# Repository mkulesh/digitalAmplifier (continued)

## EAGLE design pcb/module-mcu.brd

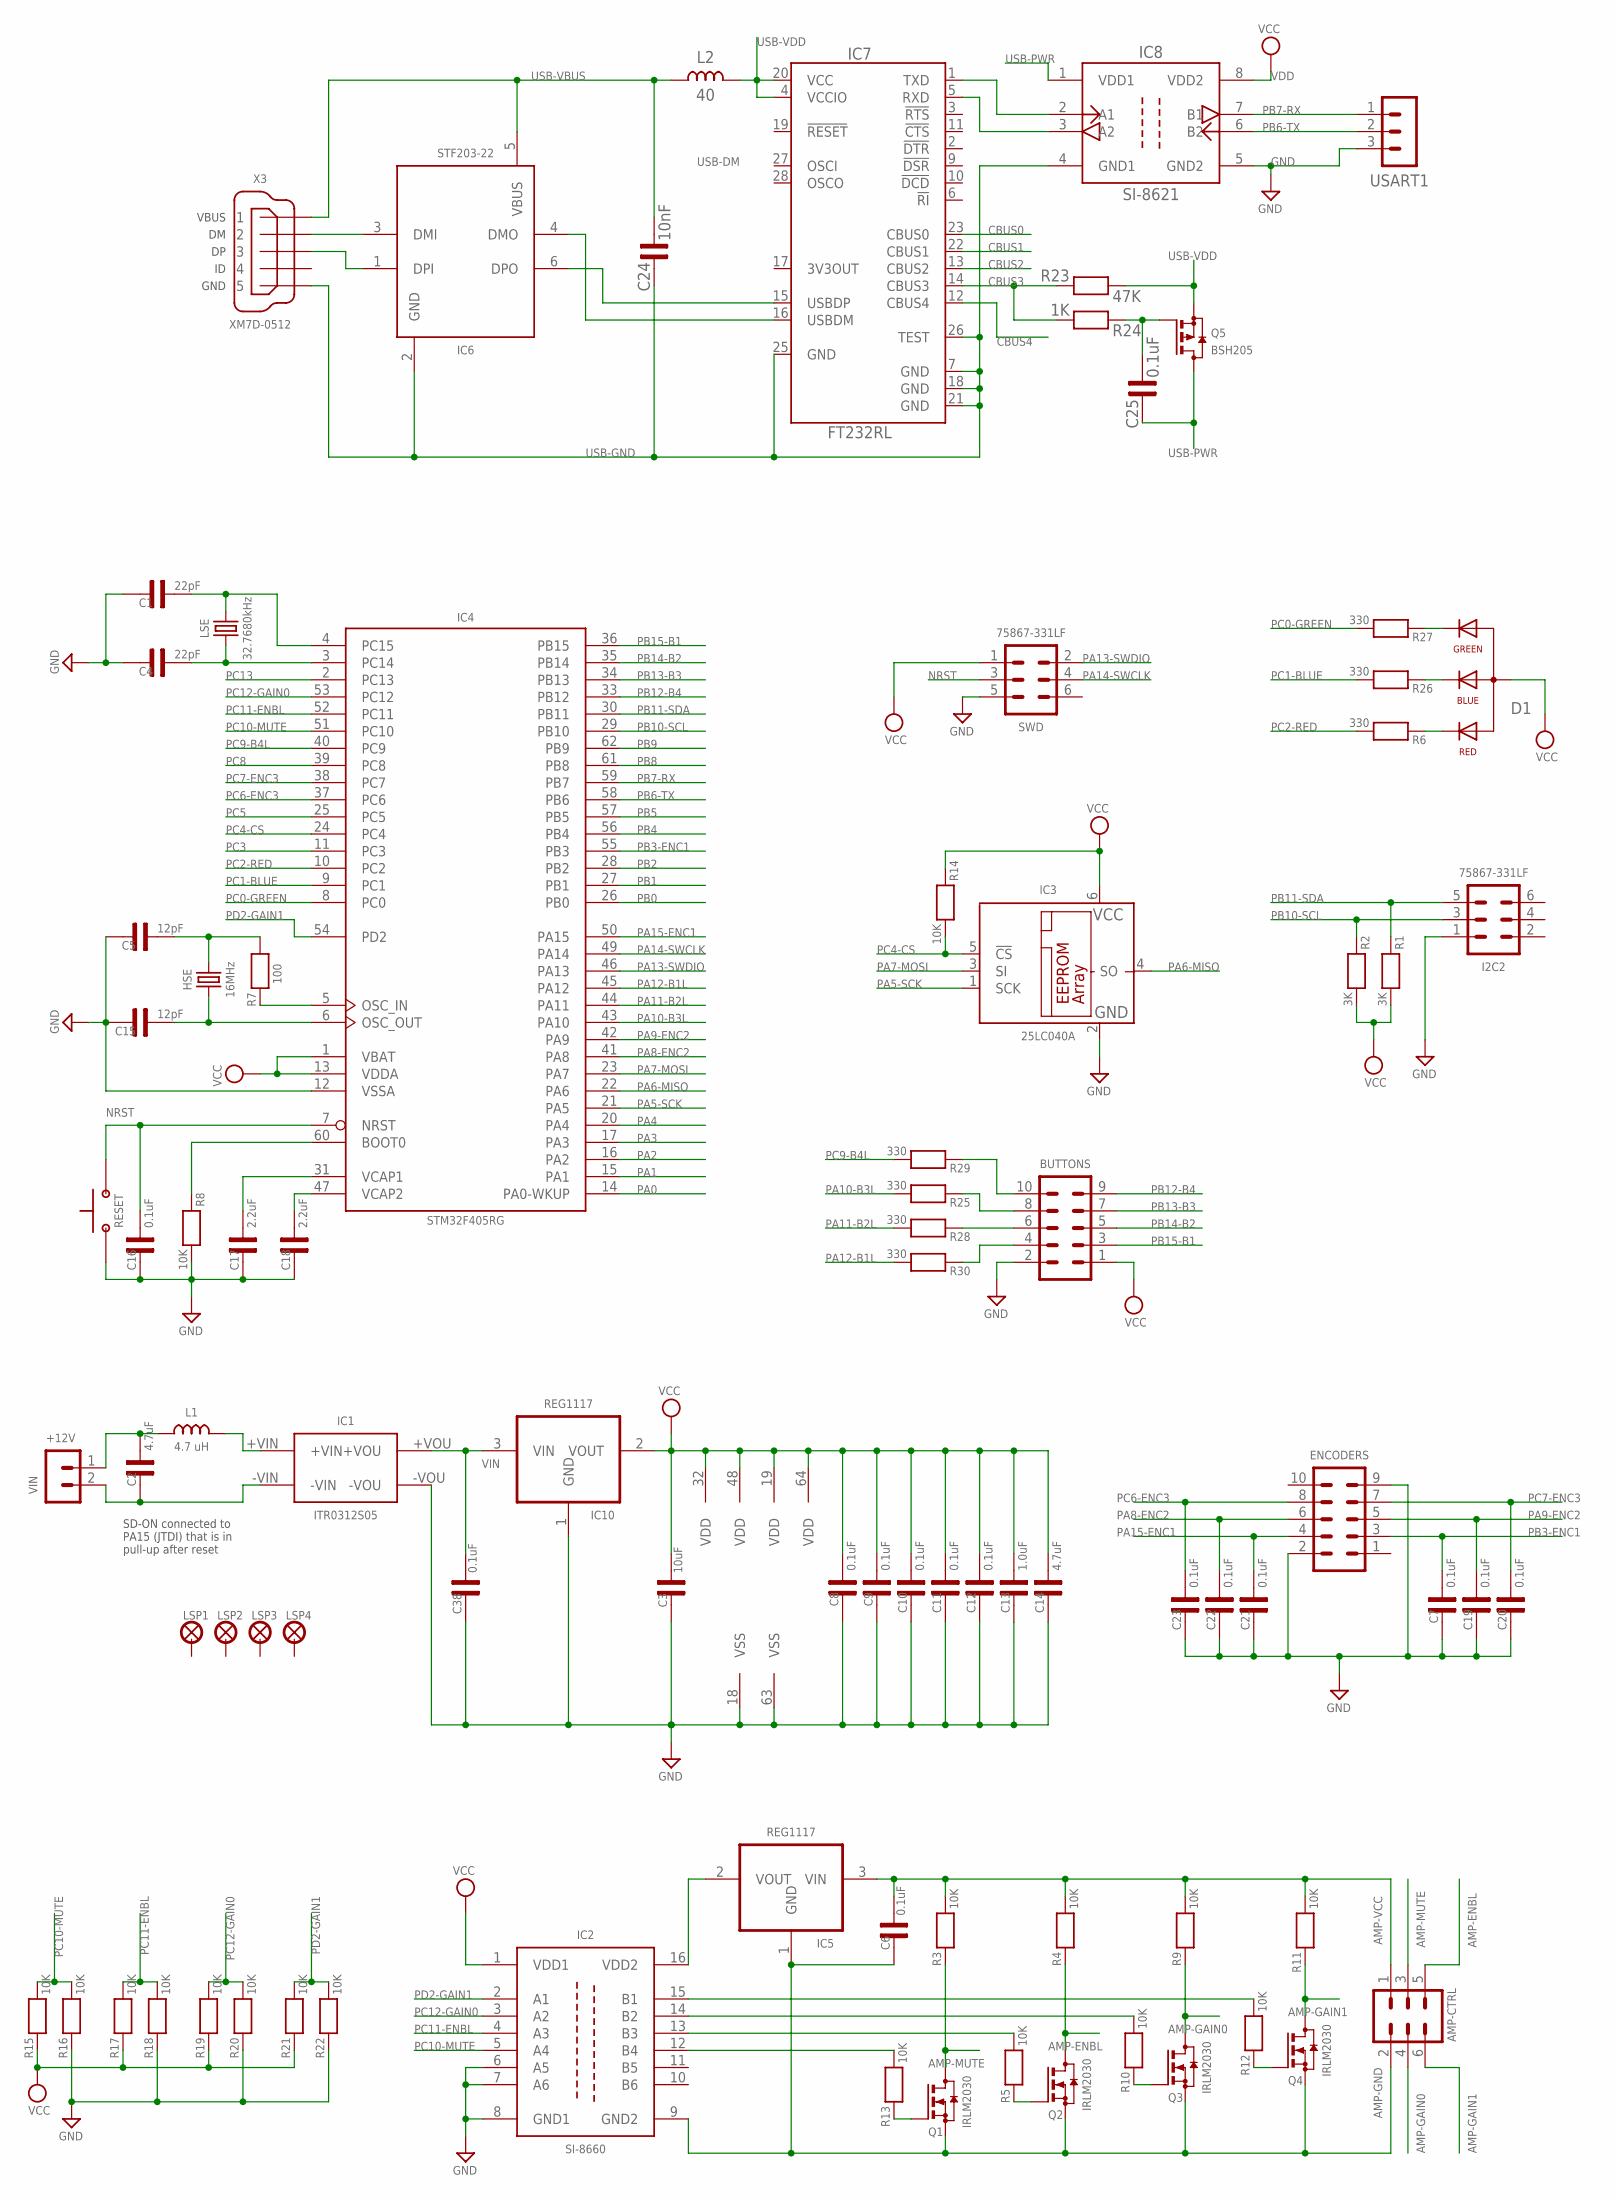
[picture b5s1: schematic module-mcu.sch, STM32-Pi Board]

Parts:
AMP-CTRL: MA03-2PL; MA03-2
BUTTONS: MA05-2
C1, C4: 22pF; C0805
C2: 4.7uF; C1206
C3: 10uF; C0805
C5, C15: 12pF; C0805
C6, C7, C8, C9, C10, C11, C12, C16, C19, C20, C21, C22, C23, C25, C38: 0.1uF; C0805
C13: 1.0uF; C0805
C14: 4.7uF; C0805
C17, C18: 2.2uF; C0805
C24: 10nF; C0805
D1: RGB-LED3X1MM; RGB-LED-SMD-3X1
ENCODERS: MA05-2
HSE: 16MHz; Q-HC-46X
I2C2: 75867-331LF; MA03-2
IC1: ITR0312S05
IC2: SI-8660; SO16
IC3: 25LC040A; SOT23-6
IC4: STM32F405RG; LQFP64
IC5, IC10: REG1117; SOT223
IC6: STF203-22; SC70-6
IC7: FT232RL; SSOP28
IC8: SI-8621; SOIC-8
L1: 4.7 uH; L0805
L2: 40; L0805
LSE: 32.7680kHz; Q-CM7V-T1A
LSP1, LSP2, LSP3, LSP4: LSP27
Q1, Q2, Q3, Q4: IRLM2030; SOT23
Q5: BSH205; SOT23
R1, R2: 3K; R0805
R3, R4, R5, R8, R9, R10, R11, R12, R13, R14, R15, R16, R17, R18, R19, R20, R21, R22: 10K; R0805
R6, R25, R26, R27, R28, R29, R30: 330; R0805
R7: 100; R0805
R23: 47K; R0805
R24: 1K; R0805
RESET: BUTTON-FSM14JRT
SWD: 75867-331LF; MA03-2-BLUE
USART1: MA03-1PL; MA03-1
VIN: MA02-1GREEN; MA02-1-GREEN
X3: XM7D-0512

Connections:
AMP-ENBL: AMP-CTRL.5, Q2.3 (D), R4.1
AMP-GAIN0: AMP-CTRL.4, Q3.3 (D), R9.1
AMP-GAIN1: AMP-CTRL.6, Q4.3 (D), R11.1
AMP-GND: AMP-CTRL.2, C6.1, IC2.9 (GND2), IC5.1 (GND), Q1.2 (S), Q2.2 (S), Q3.2 (S), Q4.2 (S)
AMP-MUTE: AMP-CTRL.3, Q1.3 (D), R3.1
AMP-VCC: AMP-CTRL.1, C6.2, IC5.3 (VIN), R3.2, R4.2, R9.2, R11.2
BOOT: IC4.60 (BOOT0), R8.1
CBUS0: IC7.23 (CBUS0)
CBUS1: IC7.22 (CBUS1)
CBUS2: IC7.13 (CBUS2)
CBUS3: IC7.14 (CBUS3), R23.1, R24.2
CBUS4: IC7.12 (CBUS4)
GND: BUTTONS.2, C1.1, C3.1, C4.1, C5.1, C7.1, C8.1, C9.1, C10.1, C11.1, C12.1, C13.1, C14.1, C15.1, C16.1, C17.1, C18.1, C19.1, C20.1, C21.1, C22.1, C23.1, C38.1, ENCODERS.2, ENCODERS.9, I2C2.1, IC1.-VOU, IC2.6 (A5), IC2.7 (A6), IC2.8 (GND1), IC3.2 (GND), IC4.12 (VSSA), IC4.18 (VSS), IC4.63 (VSS), IC8.5 (GND2), IC10.1 (GND), R8.2, R16.1, R18.1, R20.1, R22.1, RESET.P$1 (1), SWD.5, USART1.3
unnamed: C2.1, IC1.-VIN, VIN.2
unnamed: D1.P$1 (AR), R6.1
unnamed: IC4.5 (OSC_IN), R7.1
unnamed: IC1.+VIN, L1.2
unnamed: C2.2, L1.1, VIN.1
unnamed: Q2.1 (G), R5.1
unnamed: Q1.1 (G), R13.1
unnamed: IC2.12 (B4), R13.2
unnamed: IC2.13 (B3), R5.2
unnamed: Q3.1 (G), R10.1
unnamed: IC2.14 (B2), R10.2
unnamed: Q4.1 (G), R12.1
unnamed: IC2.15 (B1), R12.2
unnamed: IC2.16 (VDD2), IC5.2 (VOUT)
unnamed: IC6.1 (DPI), X3.3
unnamed: D1.P$4 (AB), R26.1
unnamed: IC6.3 (DMI), X3.2
unnamed: IC7.1 (TXD), IC8.2 (A1)
unnamed: IC7.5 (RXD), IC8.3 (A2)
unnamed: C25.2, Q5.1 (G), R24.1
unnamed: BUTTONS.4, R30.1
unnamed: BUTTONS.6, R28.1
unnamed: BUTTONS.8, R25.1
unnamed: BUTTONS.10, R29.1
unnamed: C5.2, HSE.1, R7.2
unnamed: D1.P$3 (AG), R27.1
unnamed: C15.2, HSE.2, IC4.6 (OSC_OUT)
NRST: C16.2, IC4.7 (NRST), RESET.P$2 (2), SWD.3
PA0: IC4.14 (PA0-WKUP)
PA1: IC4.15 (PA1)
PA2: IC4.16 (PA2)
PA3: IC4.17 (PA3)
PA4: IC4.20 (PA4)
PA5-SCK: IC3.1 (SCK), IC4.21 (PA5)
PA6-MISO: IC3.4 (SO), IC4.22 (PA6)
PA7-MOSI: IC3.3 (SI), IC4.23 (PA7)
PA8-ENC2: C22.2, ENCODERS.6, IC4.41 (PA8)
PA9-ENC2: C19.2, ENCODERS.5, IC4.42 (PA9)
PA10-B3L: IC4.43 (PA10), R25.2
PA11-B2L: IC4.44 (PA11), R28.2
PA12-B1L: IC4.45 (PA12), R30.2
PA13-SWDIO: IC4.46 (PA13), SWD.2
PA14-SWCLK: IC4.49 (PA14), SWD.4
PA15-ENC1: C21.2, ENCODERS.4, IC4.50 (PA15)
PB0: IC4.26 (PB0)
PB1: IC4.27 (PB1)
PB2: IC4.28 (PB2)
PB3-ENC1: C7.2, ENCODERS.3, IC4.55 (PB3)
PB4: IC4.56 (PB4)
PB5: IC4.57 (PB5)
PB6-TX: IC4.58 (PB6), IC8.6 (B2), USART1.2
PB7-RX: IC4.59 (PB7), IC8.7 (B1), USART1.1
PB8: IC4.61 (PB8)
PB9: IC4.62 (PB9)
PB10-SCL: I2C2.3, IC4.29 (PB10), R2.1
PB11-SDA: I2C2.5, IC4.30 (PB11), R1.1
PB12-B4: BUTTONS.9, IC4.33 (PB12)
PB13-B3: BUTTONS.7, IC4.34 (PB13)
PB14-B2: BUTTONS.5, IC4.35 (PB14)
PB15-B1: BUTTONS.3, IC4.36 (PB15)
PC0-GREEN: IC4.8 (PC0), R27.2
PC1-BLUE: IC4.9 (PC1), R26.2
PC2-RED: IC4.10 (PC2), R6.2
PC3: IC4.11 (PC3)
PC4-CS: IC3.5 (!CS), IC4.24 (PC4), R14.2
PC5: IC4.25 (PC5)
PC6-ENC3: C23.2, ENCODERS.8, IC4.37 (PC6)
PC7-ENC3: C20.2, ENCODERS.7, IC4.38 (PC7)
PC8: IC4.39 (PC8)
PC9-B4L: IC4.40 (PC9), R29.2
PC10-MUTE: IC2.5 (A4), IC4.51 (PC10), R15.2, R16.2
PC11-ENBL: IC2.4 (A3), IC4.52 (PC11), R17.2, R18.2
PC12-GAIN0: IC2.3 (A2), IC4.53 (PC12), R19.2, R20.2
PC13: IC4.2 (PC13)
PD2-GAIN1: IC2.2 (A1), IC4.54 (PD2), R21.2, R22.2
Q2M: C4.2, IC4.3 (PC14), LSE.1
Q2P: C1.2, IC4.4 (PC15), LSE.2
USB-DM: IC6.4 (DMO), IC7.16 (USBDM)
USB-DP: IC6.6 (DPO), IC7.15 (USBDP)
USB-GND: C24.1, IC6.2 (GND), IC7.7 (GND), IC7.18 (GND), IC7.21 (GND), IC7.25 (GND), IC7.26 (TEST), IC8.4 (GND1), X3.5
USB-PWR: C25.1, IC8.1 (VDD1), Q5.3 (D)
USB-VBUS: C24.2, IC6.5 (VBUS), L2.1, X3.1
USB-VDD: IC7.4 (VCCIO), IC7.20 (VCC), L2.2, Q5.2 (S), R23.2
VCAP3: C18.2, IC4.47 (VCAP2)
VCAP4: C17.2, IC4.31 (VCAP1)
VDD: BUTTONS.1, C3.2, C8.2, C9.2, C10.2, C11.2, C12.2, C13.2, C14.2, D1.P$2 (C), IC2.1 (VDD1), IC3.6 (VCC), IC4.1 (VBAT), IC4.13 (VDDA), IC4.19 (VDD), IC4.32 (VDD), IC4.48 (VDD), IC4.64 (VDD), IC8.8 (VDD2), IC10.2 (VOUT), R1.2, R2.2, R14.1, R15.1, R17.1, R19.1, R21.1, SWD.1
VIN: C38.2, IC1.+VOU, IC10.3 (VIN)

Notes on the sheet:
SD-ON connected to PA15 (JTDI) that is in pull-up after reset

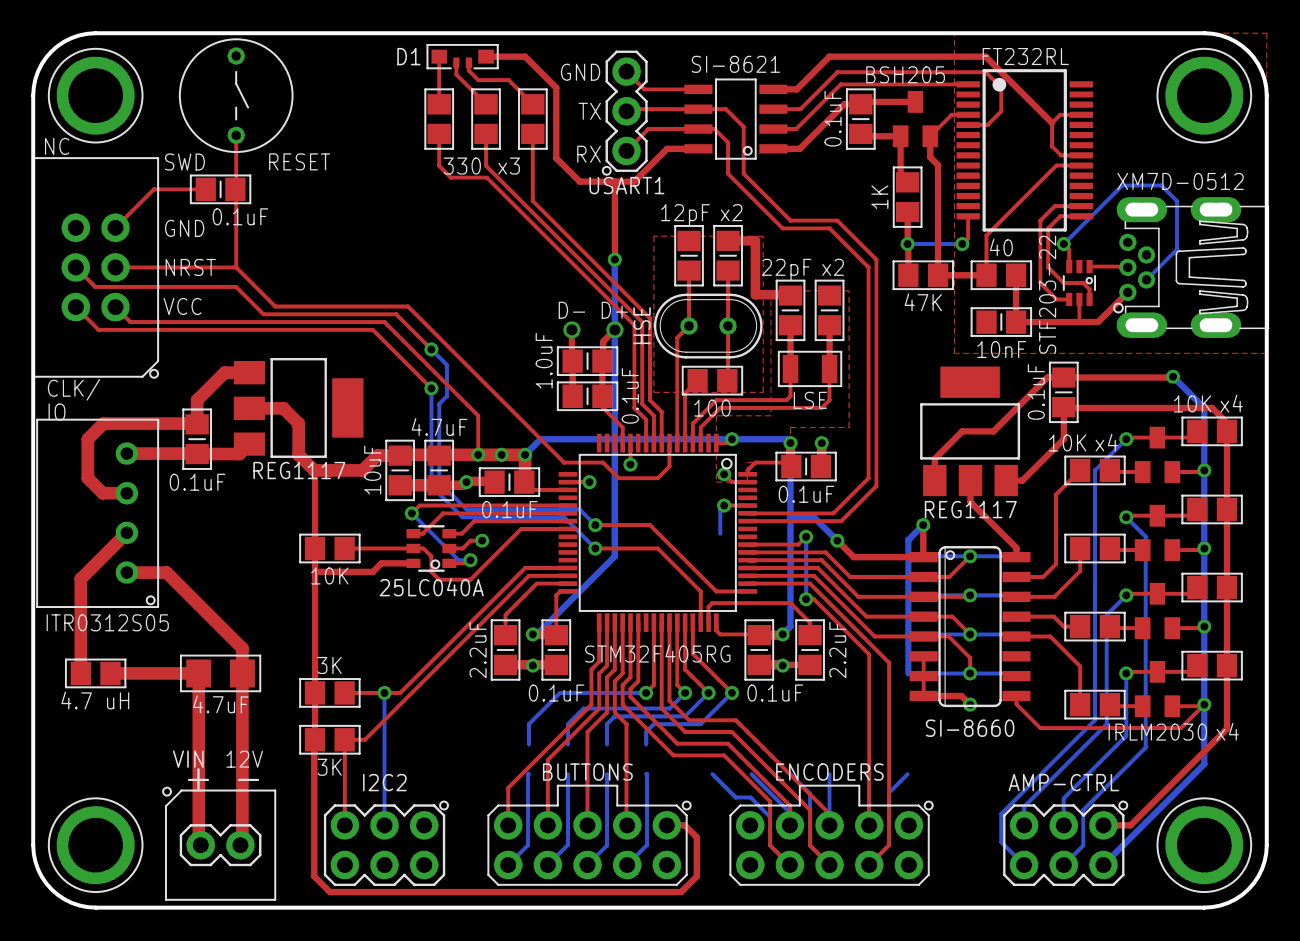
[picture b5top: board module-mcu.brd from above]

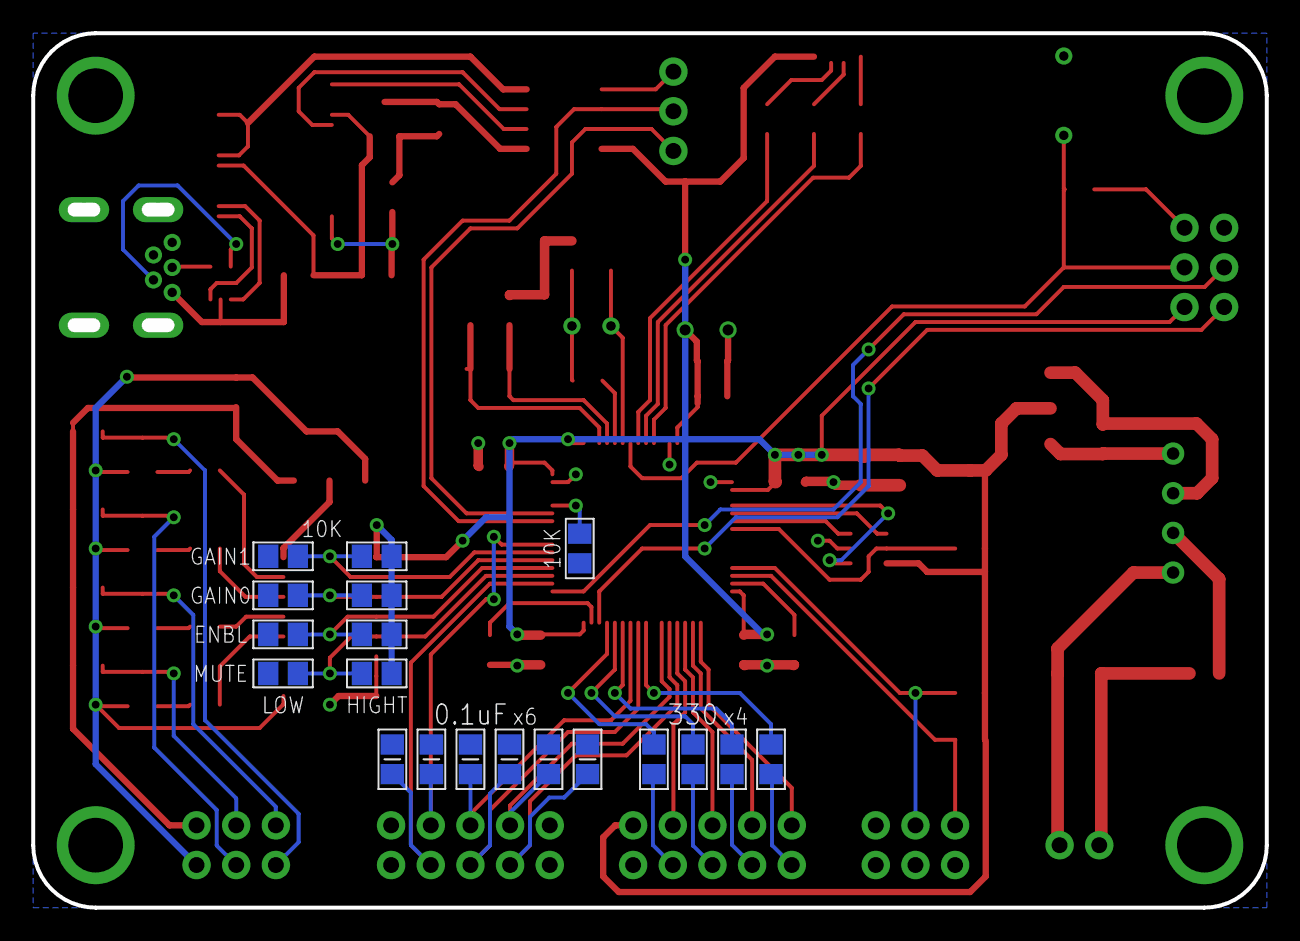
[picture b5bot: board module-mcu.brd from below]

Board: 2 copper layers, 78.4 x 55.4 mm, 88 parts (19 on the bottom side), 80 nets.

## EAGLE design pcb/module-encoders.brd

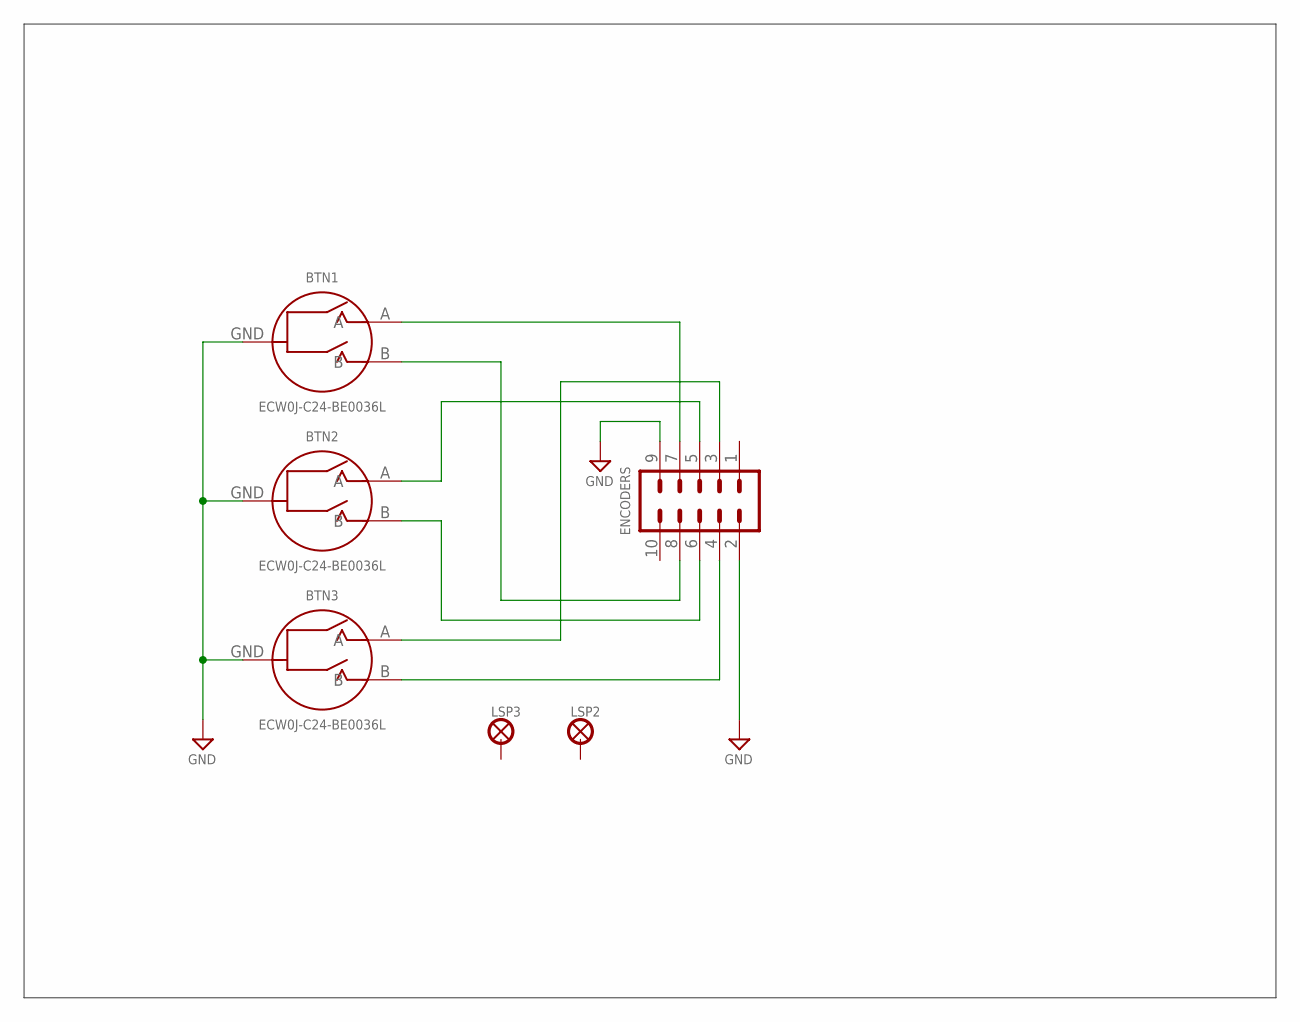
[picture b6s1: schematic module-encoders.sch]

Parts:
BTN1, BTN2, BTN3: ECW0J-C24-BE0036L; ECW0J-C24
ENCODERS: MA05-2
LSP2, LSP3: LSP27

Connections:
GND: BTN1.GND, BTN2.GND, BTN3.GND, ENCODERS.2, ENCODERS.9
unnamed: BTN3.B, ENCODERS.4
unnamed: BTN2.B, ENCODERS.6
unnamed: BTN1.B, ENCODERS.8
unnamed: BTN2.A, ENCODERS.5
unnamed: BTN1.A, ENCODERS.7
unnamed: BTN3.A, ENCODERS.3

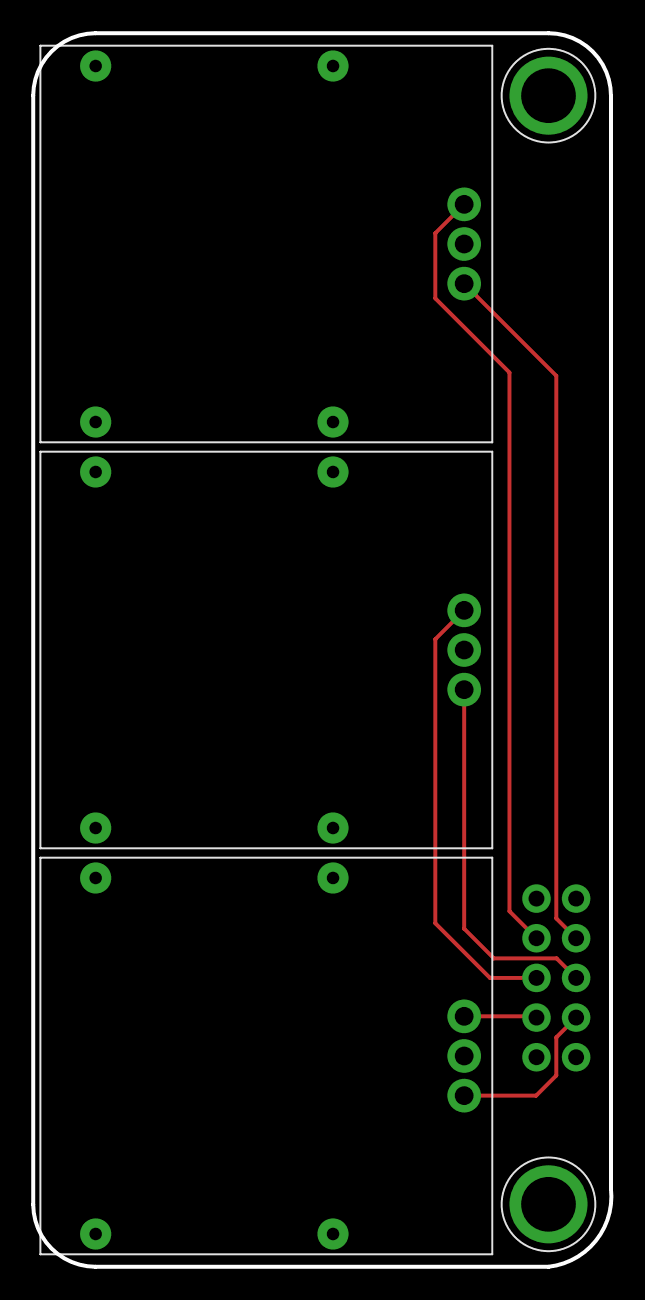
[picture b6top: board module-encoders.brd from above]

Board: 2 copper layers, 37.0 x 79.0 mm, 6 parts (1 on the bottom side), 7 nets.

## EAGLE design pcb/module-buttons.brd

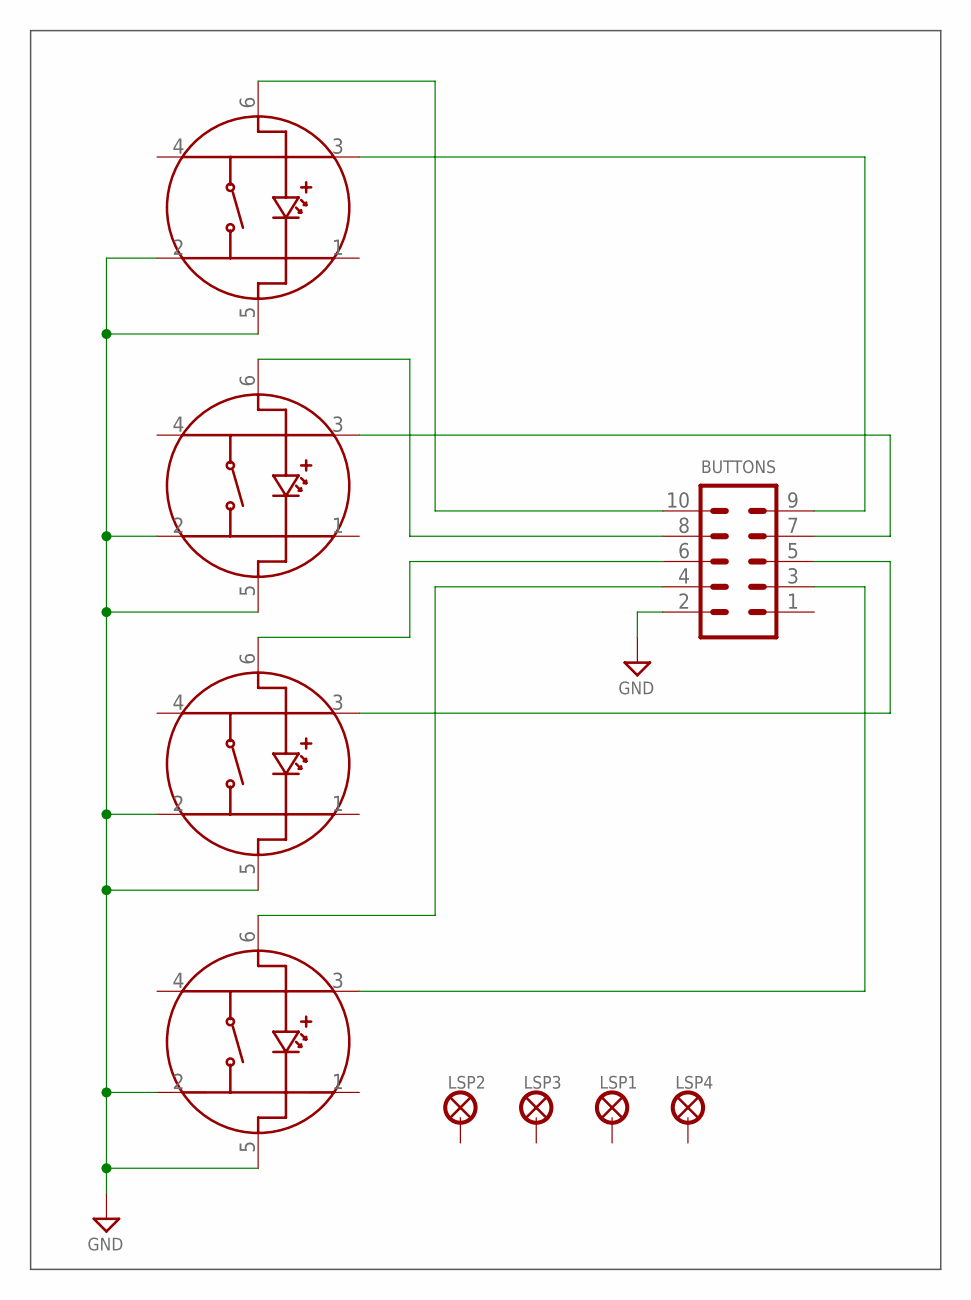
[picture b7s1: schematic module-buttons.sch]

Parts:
BTN1, BTN2, BTN3, BTN4: BUTTON-TL1265
BUTTONS: MA05-2
LSP1, LSP2, LSP3, LSP4: LSP27

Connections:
GND: BTN1.2, BTN1.5, BTN2.2, BTN2.5, BTN3.2, BTN3.5, BTN4.2, BTN4.5, BUTTONS.2
unnamed: BTN3.6, BUTTONS.6
unnamed: BTN2.3, BUTTONS.7
unnamed: BTN1.3, BUTTONS.9
unnamed: BTN3.3, BUTTONS.5
unnamed: BTN4.3, BUTTONS.3
unnamed: BTN4.6, BUTTONS.4
unnamed: BTN2.6, BUTTONS.8
unnamed: BTN1.6, BUTTONS.10

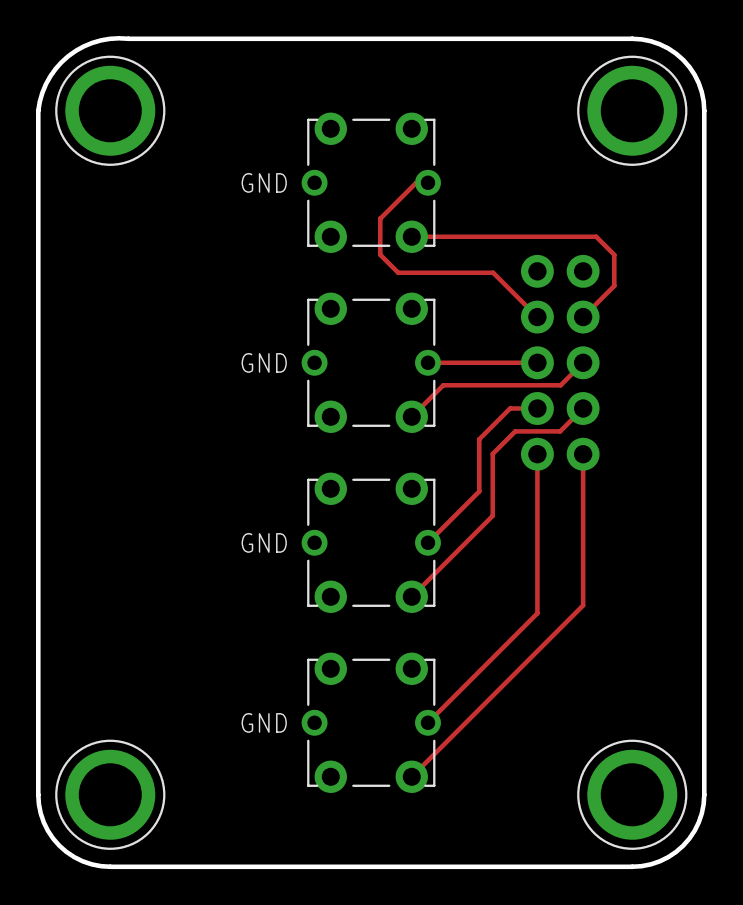
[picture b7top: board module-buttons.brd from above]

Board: 2 copper layers, 37.0 x 46.0 mm, 9 parts (1 on the bottom side), 9 nets.

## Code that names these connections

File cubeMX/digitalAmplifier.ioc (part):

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Mcu.Name=STM32F405RGTx
Mcu.Package=LQFP64
Mcu.UserName=STM32F405RGTx
PA10.GPIOParameters=GPIO_Label
PA10.GPIO_Label=btn3Led
PA10.Signal=GPIO_Output
PA11.GPIOParameters=GPIO_Label
PA11.GPIO_Label=btn2Led
PA11.Signal=GPIO_Output
PA12.GPIOParameters=GPIO_Label
PA12.GPIO_Label=btn1Led
PA12.Signal=GPIO_Output
PA13.Signal=SYS_JTMS-SWDIO
PA14.Signal=SYS_JTCK-SWCLK
PA15.GPIOParameters=GPIO_Label
PA15.GPIO_Label=enc1ch1
PA15.Signal=S_TIM2_CH1_ETR
PA2.Mode=Asynchronous
PA2.Signal=USART2_TX
PA3.Mode=Asynchronous
PA3.Signal=USART2_RX
PA5.Mode=Full_Duplex_Master
PA5.Signal=SPI1_SCK
PA6.Mode=Full_Duplex_Master
PA6.Signal=SPI1_MISO
PA7.Mode=Full_Duplex_Master
PA7.Signal=SPI1_MOSI
PA8.GPIOParameters=GPIO_Label
PA8.GPIO_Label=enc2ch1
PA8.Signal=S_TIM1_CH1
PA9.GPIOParameters=GPIO_Label
PA9.GPIO_Label=enc2ch2
PA9.Signal=S_TIM1_CH2
PB10.Mode=I2C
PB10.Signal=I2C2_SCL
PB11.Mode=I2C
PB11.Signal=I2C2_SDA
PB12.GPIOParameters=GPIO_Label
PB12.GPIO_Label=btn4
PB12.Signal=GPIO_Input
PB13.GPIOParameters=GPIO_Label
PB13.GPIO_Label=btn3
PB13.Signal=GPIO_Input
PB14.GPIOParameters=GPIO_Label
PB14.GPIO_Label=btn2
PB14.Signal=GPIO_Input
PB15.GPIOParameters=GPIO_Label
PB15.GPIO_Label=btn1
PB15.Signal=GPIO_Input
PB3.GPIOParameters=GPIO_Label
PB3.GPIO_Label=enc1ch2
PB3.Signal=S_TIM2_CH2
PB6.Mode=Asynchronous
PB6.Signal=USART1_TX
PB7.Mode=Asynchronous
PB7.Signal=USART1_RX
PB8.Mode=I2C
PB8.Signal=I2C1_SCL
PB9.Mode=I2C
PB9.Signal=I2C1_SDA
PC0.GPIOParameters=GPIO_Label
PC0.GPIO_Label=ledGreen
PC0.Signal=GPIO_Output
PC1.GPIOParameters=GPIO_Label
PC1.GPIO_Label=ledBlue
PC1.Signal=GPIO_Output
PC10.GPIOParameters=GPIO_Label
PC10.GPIO_Label=ampMute
PC10.Signal=GPIO_Input
PC11.GPIOParameters=GPIO_Label
PC11.GPIO_Label=ampEnable
PC11.Signal=GPIO_Output
PC12.GPIOParameters=GPIO_Label
PC12.GPIO_Label=ampGain0
PC12.Signal=GPIO_Output
PC14-OSC32_IN.Mode=LSE-External-Oscillator
PC14-OSC32_IN.Signal=RCC_OSC32_IN
PC15-OSC32_OUT.Mode=LSE-External-Oscillator
PC15-OSC32_OUT.Signal=RCC_OSC32_OUT
PC2.GPIOParameters=GPIO_Label
PC2.GPIO_Label=ledRed
PC2.Signal=GPIO_Output
PC4.GPIOParameters=GPIO_Label
PC4.GPIO_Label=SPI1_CS
PC4.Signal=GPIO_Output
PC6.GPIOParameters=GPIO_Label
PC6.GPIO_Label=enc3ch1
PC6.Signal=S_TIM3_CH1
PC7.GPIOParameters=GPIO_Label
PC7.GPIO_Label=enc3ch2
PC7.Signal=S_TIM3_CH2
PC9.GPIOParameters=GPIO_Label
PC9.GPIO_Label=btn4Led
PC9.Signal=GPIO_Output
PD2.GPIOParameters=GPIO_Label
PD2.GPIO_Label=ampGain1
PD2.Signal=GPIO_Output
PH0-OSC_IN.Mode=HSE-External-Oscillator
PH0-OSC_IN.Signal=RCC_OSC_IN
PH1-OSC_OUT.Mode=HSE-External-Oscillator
PH1-OSC_OUT.Signal=RCC_OSC_OUT
RCC.HSE_VALUE=25000000
RCC.SYSCLKFreq_VALUE=72000000
RCC.SYSCLKSource=RCC_SYSCLKSOURCE_PLLCLK
board=custom

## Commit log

2021-05-24 Added gitignore
2023-07-21 Added description
